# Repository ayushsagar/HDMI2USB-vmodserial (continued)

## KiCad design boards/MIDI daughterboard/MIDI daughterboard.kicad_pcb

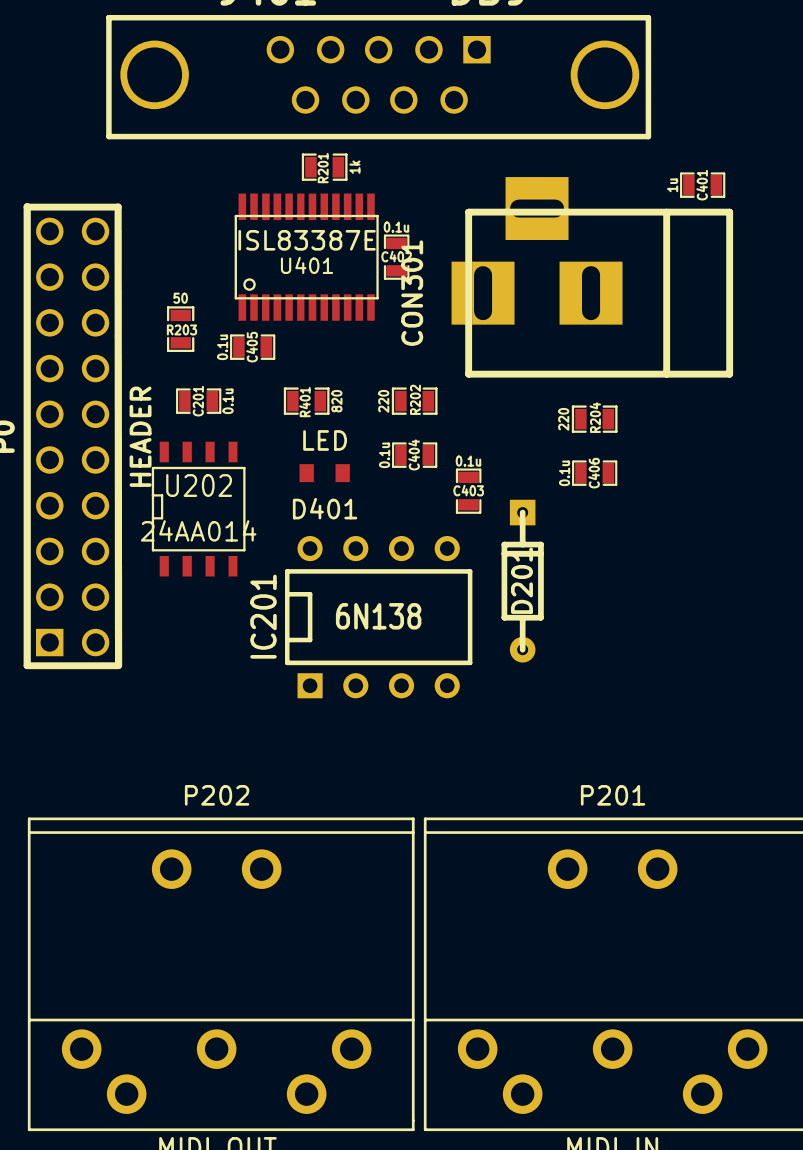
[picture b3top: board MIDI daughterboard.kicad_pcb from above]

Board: 2 copper layers, 22 parts (0 on the bottom side), 30 nets, no tracks yet.

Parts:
C201, C402, C403, C404, C405, C406: 0.1u; SM0603_Capa
C401: 1u; SM0603_Capa
CON301: BARREL_JACK
D201: 1N914; DO-35
D401: LED; Vishay_SMD_MiniLED
IC201: 6N138; DIP-8__300
J401: DB9; DB9FD
P0: HEADER; pin_array_10x2
P201: MIDI_IN; CUI_SDS-50J
P202: MIDI_OUT; CUI_SDS-50J
R201: 1k; SM0603_Resistor
R202, R204: 220; SM0603_Resistor
R203: 50; SM0603_Resistor
R401: 820; SM0603_Resistor
U202: 24AA014; SO8N
U401: ISL83387E; tssop-24

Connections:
/MIDI standalone/A0: P0.8, U202.1
/MIDI standalone/A1: P0.9, U202.2
/MIDI standalone/A2: P0.10, U202.3
/MIDI standalone/GND: C201.1, P0.12, U202.4, U202.7
/MIDI standalone/GND_ISO: C401.2, C402.2, C403.2, C404.2, CON301.2, D401.2, IC201.5, J401.5, P0.5, P0.16, P202.2, U401.11, U401.22
/MIDI standalone/RS232 adapter block/A_CTS: J401.8, U401.20
/MIDI standalone/RS232 adapter block/A_DSR: J401.6, U401.19
/MIDI standalone/RS232 adapter block/A_DTR: J401.4, U401.16
/MIDI standalone/RS232 adapter block/A_RTS: J401.7, U401.17
/MIDI standalone/RS232 adapter block/A_RX: J401.2, U401.21
/MIDI standalone/RS232 adapter block/A_TX: J401.3, U401.18
/MIDI standalone/RX_ISO: IC201.6, P0.3, R201.2, U401.7
/MIDI standalone/SCL: P0.14, U202.6
/MIDI standalone/SDA: P0.13, U202.5
/MIDI standalone/TX_ISO: P0.2, P202.5, U401.14
/MIDI standalone/VCC_3V3: P0.11, R203.1
/MIDI standalone/VCC_5V_ISO: C401.1, C402.1, CON301.1, IC201.8, P0.6, R201.1, R204.1, U401.15, U401.23, U401.24
unnamed: P202.4, R204.2
unnamed: P201.5, R202.2
unnamed: D201.1, IC201.3, R202.1
unnamed: D201.2, IC201.2, P201.4
unnamed: C201.2, R203.2, U202.8
unnamed: D401.1, R401.1
unnamed: R401.2, U401.9
unnamed: C406.2, U401.5
unnamed: C404.1, U401.6
unnamed: C405.1, U401.1
unnamed: C405.2, U401.3
unnamed: C406.1, U401.4
unnamed: C403.1, U401.2

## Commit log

2014-06-21 Added mechanical data and restructured folders
2014-06-22 Done most of top level design
2014-06-22 Completed data and power isolation sheets
2014-06-22 ID controller complete, bypass caps added in data isolation
2014-06-23 ID detection changed from RC to EEPROM based, D.board pinout changed, PIC18F85J94 added
2014-06-23 Added NC pin to D.board pinout for better elec. isolation
2014-06-23 Completed PIC 18 USB sheet; Motherboard schematic done
2014-06-23 Netlist DRC pass - fixed pins types, incorrect connections, added PWRFLAGS
2014-06-23 Added ISL83387E, deleted discarded daughterboard.sch
2014-06-23 Changed project name Main to Motherboard to avoid confusion with independent daughterboard projects to be created
2014-06-23 Fixed major flaw in autodetection circuit - daughterboard header pinout changed to set address of ROMs depending on slot
2014-06-23 Updated notes and sheet names
2014-06-23 Fixed Csmall not showing up in some versions of kicad. Fixed C308
2014-06-23 Removed ID controller.sch
2014-06-24 Added .gitignore
2014-06-24 fixed untracked files
2014-06-24 Changed UART debug connector from 2 pin to 4 pin and annotated unannotated parts
2014-06-24 Renamed Daughterboard.sch to Daughterboard slots.sch to avoid confusion
2014-06-24 Added note about A and B postfix to Data isolation sheet
2014-06-24 Added TRS jack drawing
2014-06-25 Changed Motherboard.sch to show bus connection
2014-06-25 Organized file structure
2014-06-25 Changed pins in PIC18F85J94.lib to mention 2nd I2C port
2014-06-25 Added LED mech drawing for LED daughterboard
2014-06-25 Added OSC pins to PIC18F85J94.lib
2014-06-25 Major changes in DTE PIC18 USB sheet
2014-06-25 Fixed DRC errors in DTE PIC18 USB sheet, changed VCC names to include voltages
2014-06-25 Fixed power pin and port names to include voltages
2014-06-25 Changed folder board to boards
2014-06-25 Moved Atlys Topside.pdf to third_party folder
2014-06-25 Updated file structure to accommodate daughterboard projects
2014-06-25 Created daughterboard project folders and templates
2014-06-25 Changed I2C pins on PIC18F85J94 to use free Port G
2014-06-25 Changed power pin/port names
2014-06-25 Changed daughterboard slots to support Digilent PMOD and changed label names
2014-06-25 Added PMOD specs
2014-06-26 Started blank RS232C dboard schematic and renamed folder
2014-06-26 Annotated parts in dboard slots sheet
2014-06-26 Filled in RS232 dboard, changed GPIO24 to GPIO16 board
2014-06-26 Changed RS-422 dboard name
2014-06-26 Added daughterboard mech drawings
2014-06-26 Completed RS232C daughterboard
2014-06-26 Fixed errors in RS232C daughterboard, ERC passed
2014-06-26 Improved main sheet of RS232C daughterboard
2014-06-26 Added currentlimiting resistor to RS232 dboard eeprom
2014-06-26 Updated PIC18F USB pin mapping, connections to be made
2014-06-26 Updated templates of all dboards with commonalities of all dboards
2014-06-26 Updated PIC18 USB sheet, top sheet connections remaining
2014-06-26 GPIO-8 daughterboard done; create reusable PIC16F GPIO sheet
2014-06-26 IR daughterboard done
2014-06-27 Create repository license
2014-06-29 Add ISL8491E/ISL32433E part in library
2014-06-29 Fix ISL8491E/ISL32433E part to align to grid
2014-06-29 Fix drawing error in ISL8491E/ISL32433E part
2014-06-30 Done RS422/485 Daughterboard
2014-06-30 RS422 board done
2014-06-30 Add common folder, and common input block for dboards
2014-06-30 Fix label in common input block
2014-06-30 Remove PWR_FLAG from VCC in RS232 adapter block (earlier called common input block)
2014-06-30 Update RS422 RJ-45 dboard to use RS232 adapter common block
2014-06-30 Change to 5 serial port; Connect Atlys and PIC18F SPI; Entire schematic updated
2014-06-30 Add missing dpdt_slide-switch files
2014-06-30 Change all serial connections to use BUS
2014-06-30 Fixed bus errors
2014-06-30 Fixed Power isolation block accidently deleted in e0792
2014-06-30 Divded bus among ports. Fixes #10
2014-06-30 Converted power hierarchical pins to passive
2014-07-01 Updated daughterboard header pinout in all sheets to be PMOD UART 4/4A compatible
2014-07-01 Updated LED references in PIC18FUSB. Fixes #19
2014-07-01 Removed RS232 adapter input module from RS232C daughterboard
2014-07-01 Updated GPIO8 dboard to use RS232 adapter block; Changed power hierarchy pin in RS232_adapter_block and PIC-GPIO8 sheets as passive type
2014-07-01 Updated IR dboard to use RS232 adapter block; Changed power hierarchy pins in RS232 adapter block and GPIO 8 sheet as passive type
2014-07-01 Updated IR dboard to use RS232 adapter block; Changed power hierarchy pins in RS232 adapter block and GPIO 8 sheet as passive type; Reannotated sheet
2014-07-02 Rearranged EEPROM pins in dboard slot pinout to be compatible with PMOD I2C interface
2014-07-02 Changed hierarchical pins in mboard top sheet to be tristate/BiDi instead of passive
2014-07-02 Changed LED resistor references in PIC18F USB sheet
2014-07-02 Placed power ports on top sheet of motherboard. Fixes #21
2014-07-02 Updated RS232 adapter block to include DC jack, changed power pins to passive; Changed power pins on RS422 dboard sheet to passive
2014-07-02 Connected SPI and I2C with wires in mboard top sheet
2014-07-02 Changed C622 to use std value MLCC
2014-07-02 Added Bourns MF-USMF module
2014-07-02 Added 10x2 pin array module
2014-07-02 Added LQFP80 module
2014-07-02 Fixed 10x2 pin array module
2014-07-02 Fixed again, 10x2 pin array module
2014-07-02 Updated vhdci.mod with Rohit's modifications
2014-07-02 Generated netlist; Completed CvPcb
2014-07-03 Added shield pins and fixed holes in VHDCI module
2014-07-03 Fixed mboard cmp file to use Bourns_MF-USMF.mod
2014-07-03 Created footprint for Vishay SMD MiniLED
2014-07-03 Updated gitignore to ignore kicad_pcb-bak
2014-07-03 Started motherboard PCB
2014-07-03 Added Murata 10uH module, added into library, updated CvPcb
2014-07-03 Fixed invisible references in MF-USMF, 8200 SMD, MiniLED modules
2014-07-03 Motherboard PCB components all spread out
2014-07-03 Reviewed RS232C schematics; Updated R202; Changed power hierarchical pins to passive
2014-07-03 Shifted PIC-GPIO8.sch to _common and updated related schematics
2014-07-03 Done DMX512 daughterboard schematics
2014-07-03 Added bypass capacitor to EEPROM in DMX512 dboard
2014-07-03 Fixed invalid reference to PIC-GPIO8.sch
2014-07-03 Added bypass capacitor to EEPROM in GPIO8 dboard and made cosmetic changes
2014-07-03 Added bypass capacitor to EEPROM in RS232C dboard
2014-07-03 Added bypass capacitor to EEPROM in IR dboard and made cosmetic changes
2014-07-03 Added bypass capacitor to EEPROM in GPIO16 DB25 dboard and cleaned template
2014-07-03 Added bypass capacitor to EEPROM in LED dboard and cleaned template
2014-07-03 Added bypass capacitor to EEPROM in MIDI dboard template and cleaned template
2014-07-03 Added bypass capacitor to EEPROM in RS422 dboard
2014-07-03 Created new DIN5 component with correct pinout
2014-07-03 Done MIDI daughterboard; Changed bypass capacitor in RS232_adapter_block from 0.1u to 1.0u
2014-07-03 Changed pinout conf headers in RS422 dboard and changed hierarchical pin types
2014-07-03 Changed hierarchical pin types in RS232C dboard
2014-07-03 Changed LED resistor values to 1.5k in PIC18 USB schematic
2014-07-03 Removed DB9 pinout note in GPIO-8 dboard
2014-07-03 Removed DB9 pinout note in DMX512 dboard
2014-07-03 Removed DB9 pinout note in IR dboard
2014-07-03 GPIO16 DB25 Daughterboard done
2014-07-03 Added DB25 pinout note to GPIO16 DB25 Daughterboard
2014-07-03 Changed LED resistor in RS232C dboard to 820R to be 3.3-5V compatible
2014-07-03 Run CvPcb on RS232C dboard. Completed footprint association
2014-07-03 Started RS232C dboard pcb. Spread out all components
2014-07-03 Changed header to 10x2 pin array from DIP20 in RS232C dboard
2014-07-04 Changed LED resistor to 680R in PIC18 USB
2014-07-04 Changed LED resistor values to 820R
2014-07-04 Added 10x1 pin array footprint
2014-07-04 Done CvPcb and started GPIO-8 daughterboard PCB, laid out components
2014-07-04 Added RJ45 footprint
2014-07-04 Added 8x1 pin array, DPDT switch footprints and drawing
2014-07-04 Done CvPcb on RS422 dboard
2014-07-04 Added shield pin 9 in FCI RJ45 module
2014-07-04 Started RS422 dboard PCB. Laid out components
2014-07-04 Done CvPcb on DMX512 dboard, started PCB, laid out components
2014-07-05 Created TRS jack module
2014-07-05 Created TRS jack component
2014-07-05 Updated TRS connectors in IR daughterboard
2014-07-05 Done CvPcb on IR daughterboard
2014-07-05 Fixed wrong footprint associated to DB9 on IR daughterboard
2014-07-05 Started PCB for IR daughterboard, laid out components
2014-07-05 Added DIN-5 module
2014-07-05 Done CvPcb on MIDI daughterboard
2014-07-05 Fixed IC201 assignment in MIDI dboard
2014-07-05 Started PCB for MIDI dboard and laid out components
2014-07-05 Updated daughterboard base mechanical specification for separated I2C header
2014-07-05 Created daughterboard slot schematic component
2014-07-05 Updated motherboard schematic to use new dboard_slot component
2014-07-05 Updated RS232C dboard to use new dboard_slot component
2014-07-05 Updated RS422 dboard to use new dboard_slot component
2014-07-05 Updated MIDI dboard to use new dboard_slot component
2014-07-05 Updated GPIO-8 dboard to use new dboard_slot component
2014-07-05 Updated GPIO-16 dboard to use new dboard_slot component
2014-07-05 Updated IR dboard to use new dboard_slot component
2014-07-05 Updated DMX512 dboard to use new dboard_slot component
2014-07-05 Updated LED dboard to use new dboard_slot component
2014-07-05 Created daughterboard slot module dboard_slot.mod
2014-07-05 Fixed slot addressing error
2014-07-05 Done CvPcb on motherboard with new dboard_slot module
2014-07-05 Changed U606 value to include Si8630
2014-07-06 Added boundaries to VHDCI footprint
2014-07-06 Removed unnecessary parts from vhdci module
2014-07-06 Added atlys_screw_hole module
2014-07-07 Components coagulated and arranged in motherboard PCB
2014-07-07 Edited motherboard PCB, changed canvas to A4
2014-07-07 Motherboard PCB components arranged within 2 slot area, drawn a dashed line
2014-07-08 Flipped U602, U604, U606 in data isolation sheet to make it less confusing, fixed typo in note written below
2014-07-08 Changed power pins to passive in data isolation sheet
